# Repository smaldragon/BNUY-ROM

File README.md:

# BNUY-ROM

BNUY-ROM is an homebrew discrete logic mapper for the famicom/nes, which aims to have a similar level of capabilities to common ASIC mappers, while keeping a relatively low chip count. The mapper is designed to be modular, with features that can be included or ommitted depending on the needs of a game. It is similar to BNROM, hence the name.

Its capabilities are:

* Rewritable PRG-FLASH, 32K Window:
* * **39SF0x0** - Up to 512 KiB
* * **29FxxxFT** - Up to 2048KiB
* 32KiB PRG-RAM, 8K Window
* 8KiB, 32KiB or 128KiB of CHR-RAM, 4*2K Windows
* Fixed 4-Screen Nametable Arrangement
* Scanline IRQ, with MMC5-like timing

As an in-development mapper, there is currently no iNES number attributed, nor mainstream emulator support.

Render/schematic for the prototype tht version:

# Banks

* CPU $6000-$7FFF: 8KiB switchable PRG-RAM
* CPU $8000-$FFFF: 32 KiB switchable PRG-FLASH
* PPU $0000-$07FF: 2 KiB switchable CHR-RAM Bank
* PPU $0800-$0FFF: 2 KiB switchable CHR-RAM Bank
* PPU $1000-$17FF: 2 KiB switchable CHR-RAM Bank
* PPU $1800-$1FFF: 2 KiB switchable CHR-RAM Bank

# Registers

## PRG Banking ($8000-$9FFF, write)

This register controls the banking of PRG Flash and Ram.

```
A~100x xxxx xxxx xxxx ($8000)
D~7654 3210
  ---------
  RRPP PPPP
  ||++-++++--- PRG-Flash Bank
  ++-----------PRG-Ram Bank
```

## unused ($A000-$BFFF, write)

In previous iterations of the design, this area was used for a SAM2695 soundchip. It is now unused and avaliable for potential mapper additions.

## IRQ Counter Load ($C000-$DFFF, write)

This register will load a value into a scanline counter, which decrements once per active scanline at ppu cycle 4. The counter will continuously trigger an IRQ whenever its value is 0.

There is no mechanism to stop the counter, and it will underflow to 255 if an interrupt is ignored for 1 scanline. To stop the generator from firing, a value of 255 should be written every nmi.

```
A~110x xxxx xxxx xxxx ($C000)
D~7654 3210
  ---------
  IIII IIII
  ++++-++++- 8-bit scanline counter value
```

### Details

The 8-bit down counter is clocked by bit 2 of a prescaler counter, which increments on PPU reads with A13=1 and is cleared to zero on reads with A13=0. Normally one clock signal is generated by the prescaler per active scanline (including the pre-render scanline), but manual reads from PPU_DATA during VBlank or disabling rendering mid-frame will destabilize it. This can be overcome by reading once from A13=0 and twice from A13=1, followed by reloading the counter.

Overall the mechanism is similar to MMC5's scanline counter, but using relative values like the MMC3. Unlike the MMC3, this counter allows sprites to freely use either pattern table, including both while in 8x16 mode, and its timing simplifies scroll splits on consecutive scanlines.

It uses a x4520 to detect scanlines, and either a x40103 or two x191/x193s to hold the counter value.

## CHR Banking ($E000-$FFFF, write)

If present, these registers select one of 16 2KiB CHR-RAM banks, to use for each of the 4 PPU pattern table windows.

In **8k/linear mode**, the banking register is ommited. 16KiB of RAM are mapped to the PPU Address space, including 3840 bytes of "bonus ram" above the nametables, which the CPU may use to store values.

In **32K/shared mode**, Banks 0 and 15 are shared with the 4 nametables, and should be avoided unless special care is taken. This leaves 14 banks that can be freely distributed across the 4 windows. 

In **128K/independent mode**, the register is still 4 bits wide, but now each window has their own unique set of 16 banks (by connecting the top 2 address lines of memory to ppu A11/A12), this effectively quadruples the amount of avaliable chr-ram without adding a second register chip to the board. The first 2 windows share banks 15 with the nametables

```
A~111x xxxx xxxx xx00 ($E000)
	CHR Window 0
A~111x xxxx xxxx xx01 ($E001)
	CHR Window 1
A~111x xxxx xxxx xx10 ($E002)
	CHR Window 2
A~111x xxxx xxxx xx11 ($E003)
	CHR Window 3

D~7654 3210
  ---------
  .... BBBB
       ++++- CHR Bank Select
```

This uses a single x670 4x4 register. A second register could be added to the design for an oversize variant of 512KiB (shared) or 2048KiB (independent). A design with CHR-ROM could be used instead, at the cost of losing 4-screen nametable arrangement.

# Flash Programming

Flash programming is achieved by writing a specific sequence of command bytes to particular memory addresses, during this process flash memory cannot be read as normal, and conflicting mapper registers will have their values overwritten. As such, **flash programming code must be run from the internal 2KiB console ram, and all interrupts must be disabled**.

Flash writes operate by ANDing the written byte with the existing value in memory, with the only way to set a bit being by erasing an entire sector to `$FF`.

39SF commands listen to `A0-14`, which requires clobbering the IRQ Counter, while 29F commands listen only to `A0-A11`, allowing commands to fit in the unused `$A000-$BFFF` region.

For more information check the datasheet for your particular flash chip.

## Write Byte

### 39SF0x0

```
A~$8000 D~BANK
A~$D555 D~$AA
A~$AAAA D~$55
A~$D555 D~$A0
A~ADDR  D~DATA
```

### 29FxxxFT

```
A~$8000 D~BANK
A~$AAAA D~$AA
A~$A555 D~$55
A~$AAAA D~$A0
A~ADDR  D~DATA
```

## Erase Sector

### 39SF0x0

```
A~$8000 D~BANK
A~$D555 D~$AA
A~$AAAA D~$55
A~$D555 D~$80
A~$D555 D~$AA
A~$AAAA D~$55
A~ADDR  D~$30
```
**39SF0x0** uses uniform sectors of 4KiB,

### 29FxxxFT

```
A~$8000 D~BANK
A~$AAAA D~$AA
A~$A555 D~$55
A~$AAAA D~$80
A~$AAAA D~$AA
A~$A555 D~$55
A~ADDR  D~$30
```

**29FxxxFT** uses sectors of varying sizes depending on bank:
* Last Bank: 8KiB sectors at `$8000-$9FFF`, `$A000-$BFFF`, 16KiB sector at `$C000-$FFFF`
* Second-to-Last Bank: Single 32KiB sector
* All other banks: 64KiB sectors spanning 2 banks each.

## Write/Erase End Detect

The end of a write or erase operation can be detected by reading any memory address in flash until the same value is returned twice (toggle bit method).

## Software ID

Software ID mode can be entered to detect the manufacturer, size and type of flash chip, allowing for the same rom file to be compatible with multiple board configurations. Software ID is entered using the following command sequences:

### 39SF0x0

```
A~$8000 D~$00
A~$D555 D~$AA
A~$AAAA D~$55
A~$D555 D~$90
```

### 29FxxxFT

```
A~$8000 D~$00
A~$AAAA D~$AA
A~$A555 D~$55
A~$AAAA D~$90
```

Software ID mode is exited by writing `$F0` anywhere in flash.

### Device Code ($8001, read)

* `$B5` - 39SF010 (128KiB)
* `$B6` - 39SF020 (256KiB)
* `$B7` - 39SF040  (512KiB)
* `$51` - 29F200FT (256KiB)
* `$23` - 29F400FT (512KiB)
* `$D6` - 29F800FT (1024KiB)
* `$D2` - 29F160FT (2048KiB)

# NES 2.0 Description (tentative)

**Mapper ID**: *Unassigned*

**Flags 6 (nametable layout/flashing)**

```
D~3210
  ----
  F0BM
  | |+-- Hard-Wired Arragement
  | |      0: Vertical / 4-screen
  | |      1: Horizontal
  | +--- Uses Flash Saves
  |        0: No
  |        1: Yes
  +----- 4-Screen Arrangement
           0: Hard-Wired (using CIRAM)
           1: 4-Screen (using CHR-RAM)
```

Most games will have `%1010` here.

**Flags 8 (submapper)**

```
D~7654
  ----
  FICC
  ||++-- CHR Banking Mode
  ||        0: 8K/Linear (no banking)
  ||        1: 32K/Shared (all banks avaliable in every window)
  ||        2: 128K/Independent (all windows have unique sets of banks)
  |+---- Interrupt Generator
  |         0: No IRQ
  |         1: Has IRQ
  +----- Flash Memory Type
            0: 39SF0x0 (sizes of 128K, 256K, 512K)
            1: 29FxxxFT (sizes of 256K, 512K, 1024K, 2048K)
```

**PRG-ROM, PRG-RAM and CHR-RAM size**

Size should match the memory accessible on the board.

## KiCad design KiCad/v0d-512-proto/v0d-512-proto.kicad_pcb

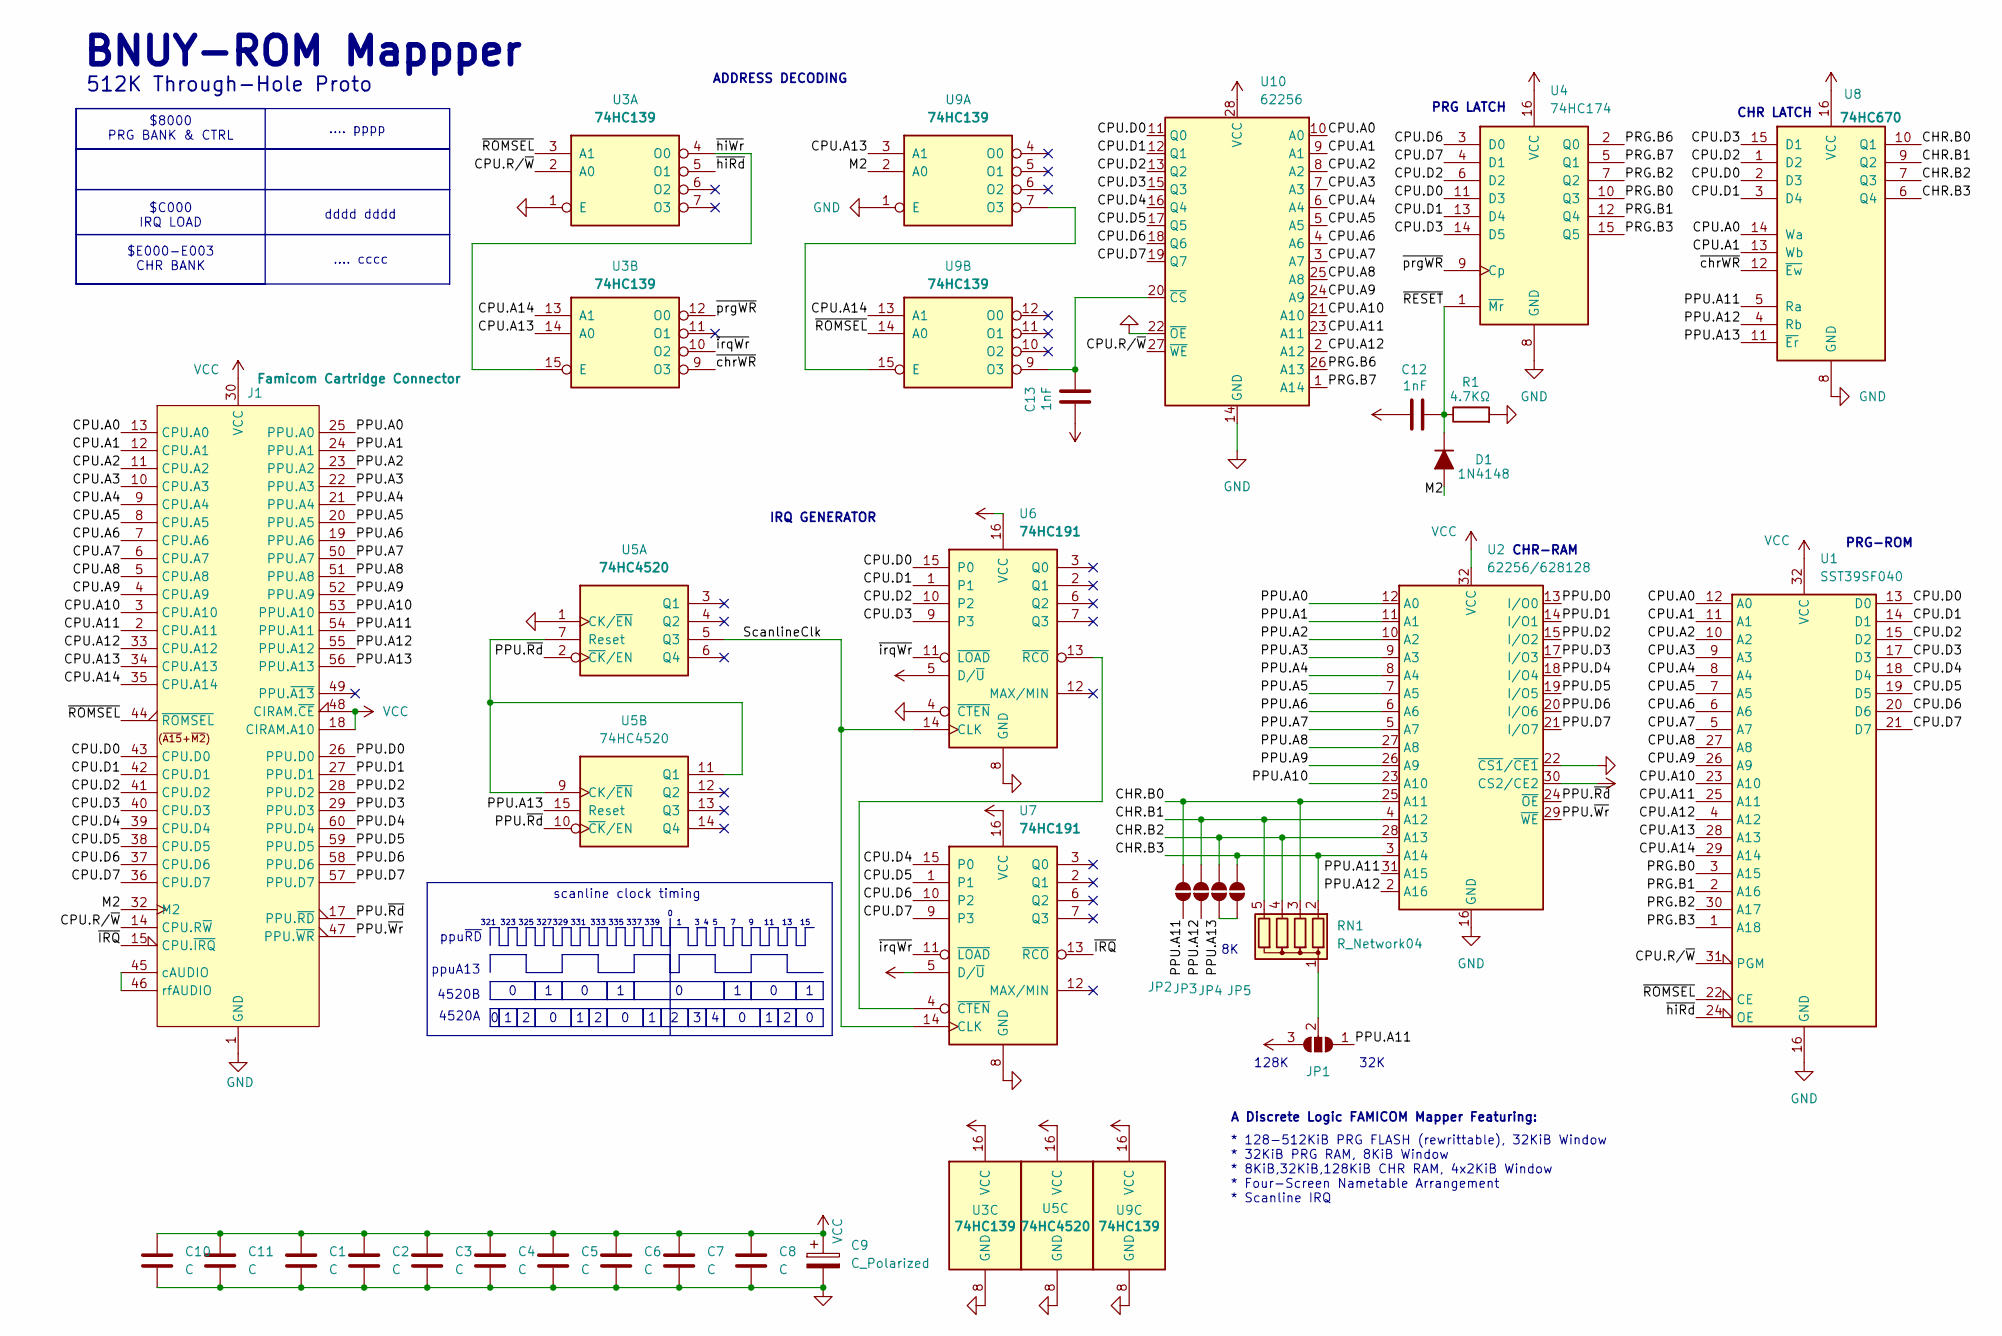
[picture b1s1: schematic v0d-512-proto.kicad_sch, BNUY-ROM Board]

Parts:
C1, C2, C3, C4, C5, C6, C7, C8, C10, C11: C; C_Disc_D3.0mm_W1.6mm_P2.50mm
C9: C_Polarized; CP_Radial_D5.0mm_P2.50mm
C12, C13: 1nF; C_Disc_D3.0mm_W1.6mm_P2.50mm
D1: 1N4148; D_DO-35_SOD27_P2.54mm_Vertical_AnodeUp
J1: Famicom Cartridge Connector; Famicom Cartridge Edge Connector (long legs)
JP1: SolderJumper_3_Open; SolderJumper-3_P1.3mm_Open_Pad1.0x1.5mm_NumberLabels
JP2, JP3, JP4, JP5: SolderJumper_2_Open; SolderJumper-2_P1.3mm_Open_Pad1.0x1.5mm
R1: 4.7KΩ; R_Axial_DIN0204_L3.6mm_D1.6mm_P2.54mm_Vertical
RN1: R_Network04; R_Array_SIP5
U1: SST39SF040; PLCC-DIP-32_THT-Socket
U2: 62256/628128; DIP-32_W15.24mm
U3, U9: 74HC139; DIP-16_W7.62mm
U4: 74HC174; DIP-16_W7.62mm
U5: 74HC4520; DIP-16_W7.62mm
U6, U7: 74HC191; DIP-16_W7.62mm
U8: 74HC670; DIP-16_W7.62mm
U10: 62256; DIP-28_W15.24mm

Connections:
/CHR.B0: JP2.1 (A), RN1.3 (R2), U2.25 (A11), U8.10 (Q1)
/CHR.B1: JP3.1 (A), RN1.5 (R4), U2.4 (A12), U8.9 (Q2)
/CHR.B2: JP4.1 (A), RN1.4 (R3), U2.28 (A13), U8.7 (Q3)
/CHR.B3: JP5.1 (A), RN1.2 (R1), U2.3 (A14), U8.6 (Q4)
/CPU.A0: J1.13 (CPU.A0), U1.12 (A0), U8.14 (Wa), U10.10 (A0)
/CPU.A1: J1.12 (CPU.A1), U1.11 (A1), U8.13 (Wb), U10.9 (A1)
/CPU.A2: J1.11 (CPU.A2), U1.10 (A2), U10.8 (A2)
/CPU.A3: J1.10 (CPU.A3), U1.9 (A3), U10.7 (A3)
/CPU.A4: J1.9 (CPU.A4), U1.8 (A4), U10.6 (A4)
/CPU.A5: J1.8 (CPU.A5), U1.7 (A5), U10.5 (A5)
/CPU.A6: J1.7 (CPU.A6), U1.6 (A6), U10.4 (A6)
/CPU.A7: J1.6 (CPU.A7), U1.5 (A7), U10.3 (A7)
/CPU.A8: J1.5 (CPU.A8), U1.27 (A8), U10.25 (A8)
/CPU.A9: J1.4 (CPU.A9), U1.26 (A9), U10.24 (A9)
/CPU.A10: J1.3 (CPU.A10), U1.23 (A10), U10.21 (A10)
/CPU.A11: J1.2 (CPU.A11), U1.25 (A11), U10.23 (A11)
/CPU.A12: J1.33 (CPU.A12), U1.4 (A12), U10.2 (A12)
/CPU.A13: J1.34 (CPU.A13), U1.28 (A13), U3.14 (A0), U9.3 (A1)
/CPU.A14: J1.35 (CPU.A14), U1.29 (A14), U3.13 (A1), U9.13 (A1)
/CPU.D0: J1.43 (CPU.D0), U1.13 (D0), U4.11 (D3), U6.15 (P0), U8.2 (D3), U10.11 (Q0)
/CPU.D1: J1.42 (CPU.D1), U1.14 (D1), U4.13 (D4), U6.1, U8.3 (D4), U10.12 (Q1)
/CPU.D2: J1.41 (CPU.D2), U1.15 (D2), U4.6 (D2), U6.10 (P2), U8.1 (D2), U10.13 (Q2)
/CPU.D3: J1.40 (CPU.D3), U1.17 (D3), U4.14 (D5), U6.9 (P3), U8.15 (D1), U10.15 (Q3)
/CPU.D4: J1.39 (CPU.D4), U1.18 (D4), U7.15 (P0), U10.16 (Q4)
/CPU.D5: J1.38 (CPU.D5), U1.19 (D5), U7.1, U10.17 (Q5)
/CPU.D6: J1.37 (CPU.D6), U1.20 (D6), U4.3 (D0), U7.10 (P2), U10.18 (Q6)
/CPU.D7: J1.36 (CPU.D7), U1.21 (D7), U4.4 (D1), U7.9 (P3), U10.19 (Q7)
/CPU.R/~W: J1.14 (CPU.R~W), U1.31 (PGM), U3.2 (A0), U10.27 (~WE)
/M2: D1.2 (A), J1.32 (M2), U9.2 (A0)
/PPU.A0: J1.25 (PPU.A0), U2.12 (A0)
/PPU.A1: J1.24 (PPU.A1), U2.11 (A1)
/PPU.A2: J1.23 (PPU.A2), U2.10 (A2)
/PPU.A3: J1.22 (PPU.A3), U2.9 (A3)
/PPU.A4: J1.21 (PPU.A4), U2.8 (A4)
/PPU.A5: J1.20 (PPU.A5), U2.7 (A5)
/PPU.A6: J1.19 (PPU.A6), U2.6 (A6)
/PPU.A7: J1.50 (PPU.A7), U2.5 (A7)
/PPU.A8: J1.51 (PPU.A8), U2.27 (A8)
/PPU.A9: J1.52 (PPU.A9), U2.26 (A9)
/PPU.A10: J1.53 (PPU.A10), U2.23 (A10)
/PPU.A11: J1.54 (PPU.A11), JP1.1 (A), JP2.2 (B), U2.31 (A15), U8.5 (Ra)
/PPU.A12: J1.55 (PPU.A12), JP3.2 (B), U2.2 (A16), U8.4 (Rb)
/PPU.A13: J1.56 (PPU.A13), JP4.2 (B), JP5.2 (B), U5.15 (Reset), U8.11 (~Er)
/PPU.D0: J1.26 (PPU.D0), U2.13 (I/O0)
/PPU.D1: J1.27 (PPU.D1), U2.14 (I/O1)
/PPU.D2: J1.28 (PPU.D2), U2.15 (I/O2)
/PPU.D3: J1.29 (PPU.D3), U2.17 (I/O3)
/PPU.D4: J1.60 (PPU.D4), U2.18 (I/O4)
/PPU.D5: J1.59 (PPU.D5), U2.19 (I/O5)
/PPU.D6: J1.58 (PPU.D6), U2.20 (I/O6)
/PPU.D7: J1.57 (PPU.D7), U2.21 (I/O7)
/PPU.~Rd: J1.17 (PPU.~RD), U2.24 (~OE), U5.2 (~CK/EN), U5.10 (~CK/EN)
/PPU.~Wr: J1.47 (PPU.~WR), U2.29 (~WE)
/PRG.B0: U1.3 (A15), U4.10 (Q3)
/PRG.B1: U1.2 (A16), U4.12 (Q4)
/PRG.B2: U1.30 (A17), U4.7 (Q2)
/PRG.B3: U1.1 (A18), U4.15 (Q5)
/PRG.B6: U4.2 (Q0), U10.26 (A13)
/PRG.B7: U4.5 (Q1), U10.1 (A14)
/ScanlineClk: U5.5 (Q3), U6.14 (CLK), U7.14 (CLK)
/~IRQ: J1.15 (CPU.~IRQ), U7.13 (~RCO)
/~RESET: C12.2, D1.1 (K), R1.1, U4.1 (~Mr)
/~ROMSEL: J1.44 (~ROMSEL), U1.22 (CE), U3.3 (A1), U9.14 (A0)
/~chrWR: U3.9 (O3), U8.12 (~Ew)
/~hiRd: U1.24 (OE), U3.5 (O1)
/~hiWr: U3.4 (O0), U3.15 (E)
/~irqWr: U3.10 (O2), U6.11 (~LOAD), U7.11 (~LOAD)
/~prgWR: U3.12 (O0), U4.9 (Cp)
GND: C1.2, C2.2, C3.2, C4.2, C5.2, C6.2, C7.2, C8.2, C9.2, C10.2, C11.2, J1.1 (GND), J1.16 (GND), R1.2, U1.16 (GND), U2.16 (GND), U2.22 (~CS1/~CE1), U3.1 (E), U3.8 (GND), U4.8 (GND), U5.1 (CK/~EN), U5.8 (GND), U6.4 (~CTEN), U6.8 (GND), U7.8 (GND), U8.8 (GND), U9.1 (E), U9.8 (GND), U10.14 (GND), U10.22 (~OE)
unnamed: J1.45 (cAUDIO), J1.46 (rfAUDIO)
unnamed: JP1.2 (C), RN1.1 (common)
unnamed: U5.7 (Reset), U5.9 (CK/~EN), U5.11 (Q1)
unnamed: U6.13 (~RCO), U7.4 (~CTEN)
unnamed: U9.7 (O3), U9.15 (E)
unnamed: C13.2, U9.9 (O3), U10.20 (~CS)
VCC: C1.1, C2.1, C3.1, C4.1, C5.1, C6.1, C7.1, C8.1, C9.1, C10.1, C11.1, C12.1, C13.1, J1.18 (CIRAM.A10), J1.30 (VCC), J1.31 (VCC), J1.48 (CIRAM.~CE), JP1.3 (B), U1.32 (VCC), U2.30 (CS2/CE2), U2.32 (VCC), U3.16 (VCC), U4.16 (VCC), U5.16 (VCC), U6.5 (D/~U), U6.16 (VCC), U7.5 (D/~U), U7.16 (VCC), U8.16 (VCC), U9.16 (VCC), U10.28 (VCC)

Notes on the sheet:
BNUY-ROM Mappper
335
321
.... pppp
* 128-512KiB PRG FLASH (rewrittable), 32KiB Window * 32KiB PRG RAM, 8KiB Window * 8KiB,32KiB,128KiB CHR RAM, 4x2KiB Window * Four-Screen Nametable Arrangement * Scanline IRQ
325
512K Through-Hole Proto
4520B
ADDRESS DECODING
327
339
ppuA13
CHR-RAM
dddd dddd
333
337
.... cccc
4520A
329
CHR LATCH
323
128K
A Discrete Logic FAMICOM Mapper Featuring:
PRG-ROM
scanline clock timing
IRQ GENERATOR
PRG LATCH
32K
331
ppu~{RD}
$8000 PRG BANK & CTRL $C000 IRQ LOAD $E000-E003 CHR BANK

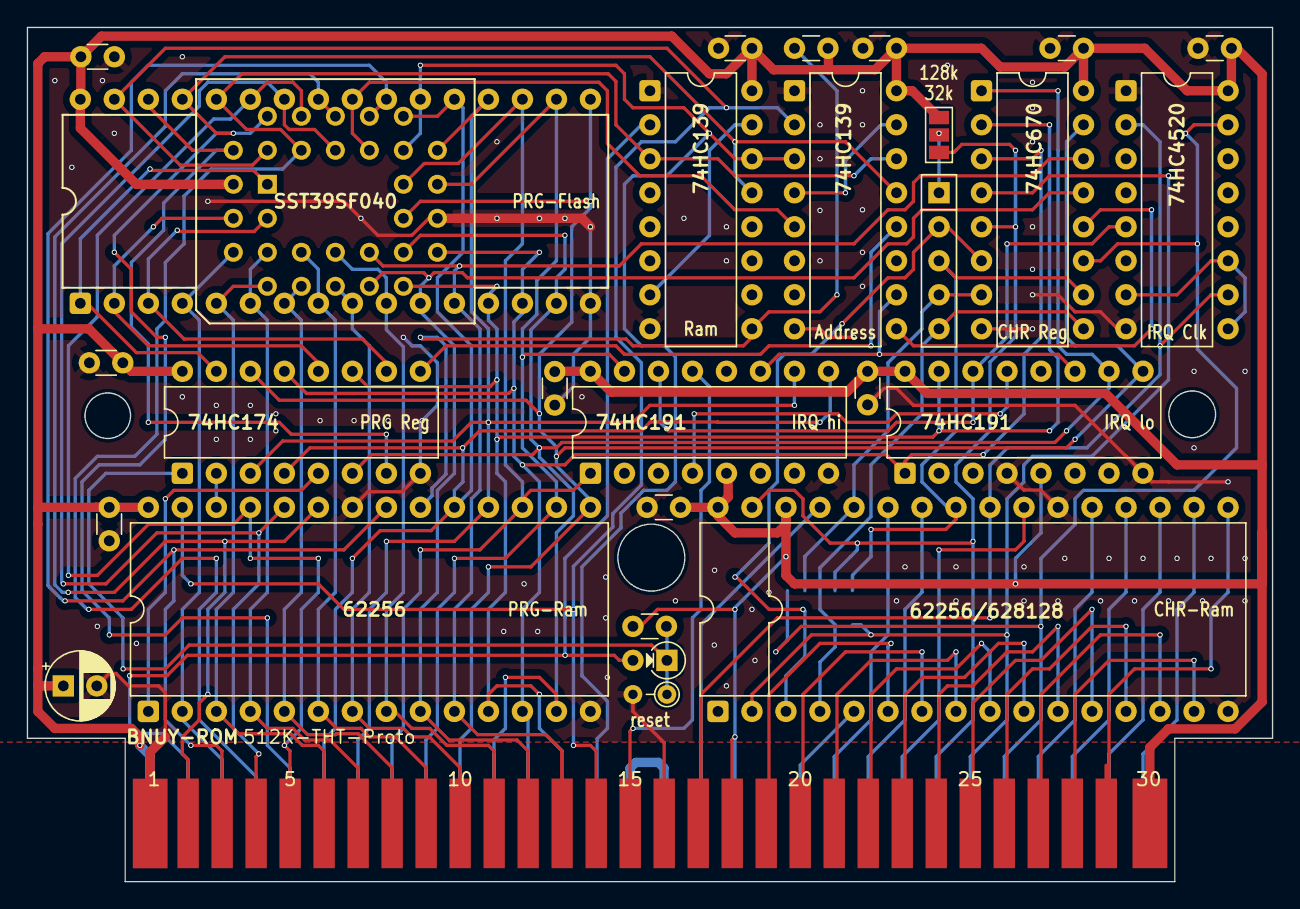
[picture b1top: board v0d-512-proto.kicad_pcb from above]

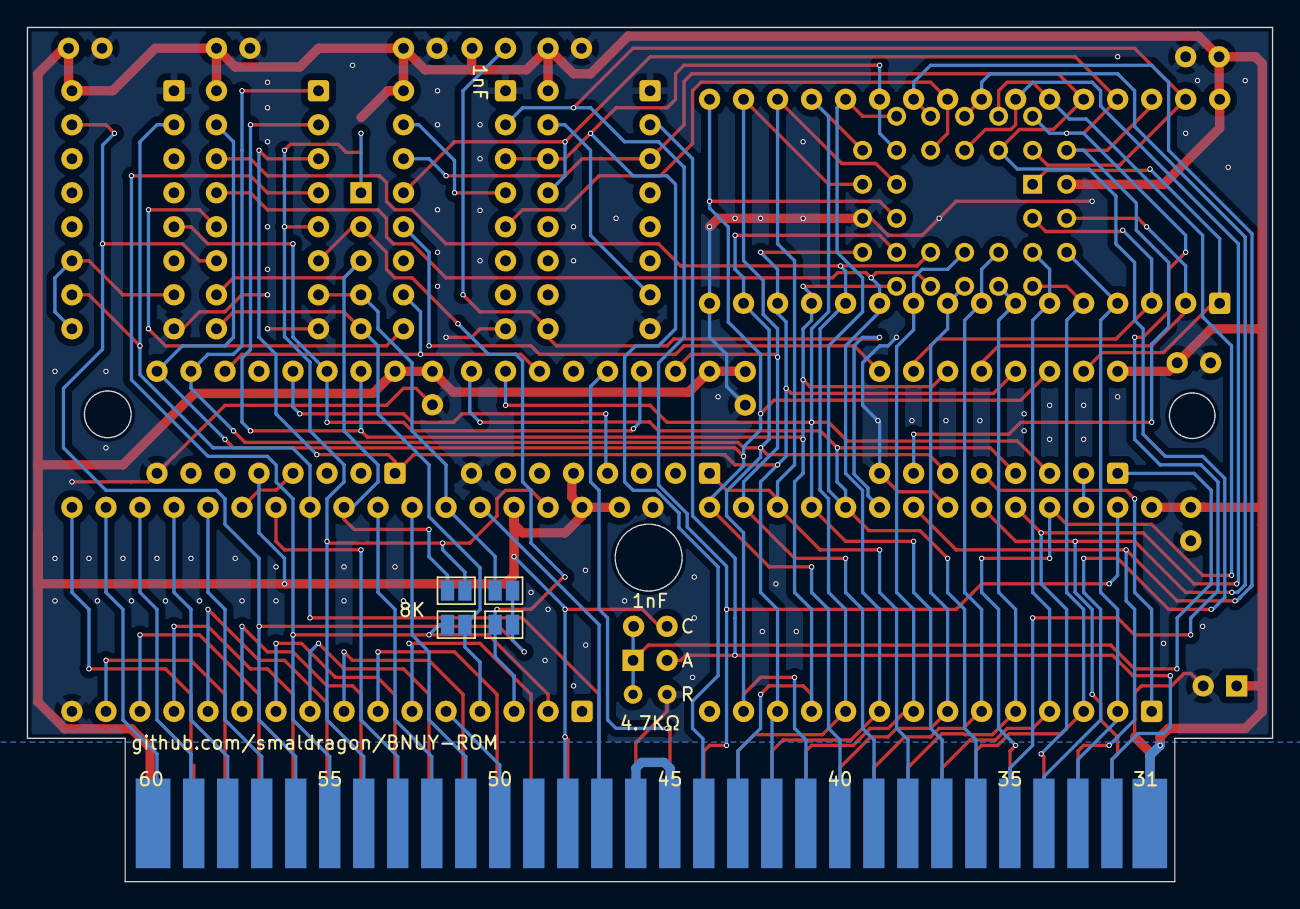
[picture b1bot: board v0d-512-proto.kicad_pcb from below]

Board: 2 copper layers, 93.0 x 63.8 mm, 32 parts (4 on the bottom side), 76 nets.

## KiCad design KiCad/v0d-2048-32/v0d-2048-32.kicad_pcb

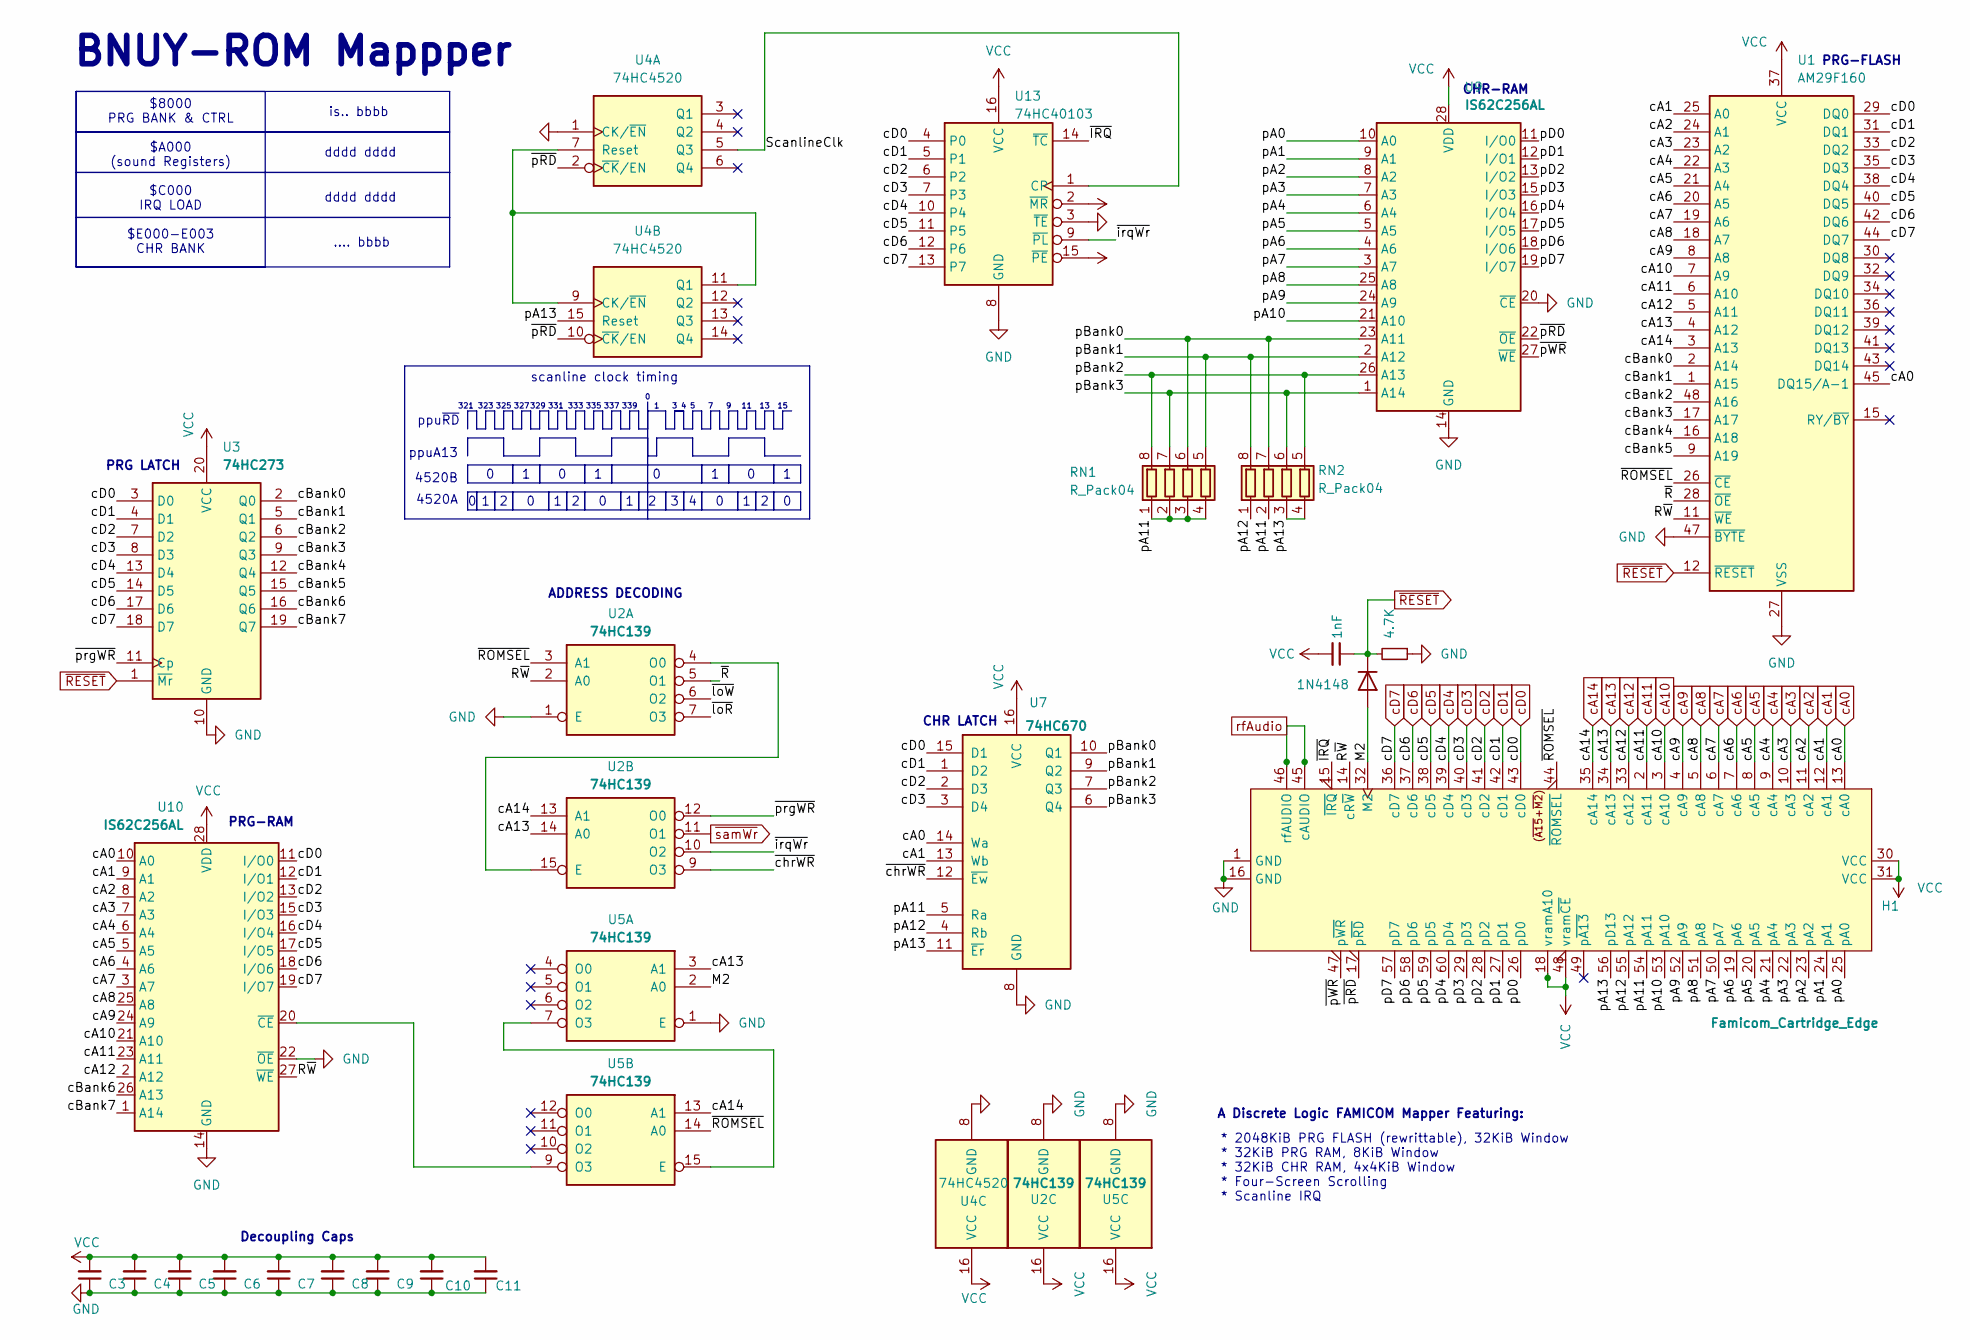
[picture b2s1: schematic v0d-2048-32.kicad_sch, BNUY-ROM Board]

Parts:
C1: 1nF; C_0603_1608Metric_Pad1.08x0.95mm_HandSolder
C3, C4, C5, C6, C7, C8, C9, C10, C11: C_Small; C_0603_1608Metric_Pad1.08x0.95mm_HandSolder
D1: 1N4148; D_0603_1608Metric_Pad1.05x0.95mm_HandSolder
H1: Famicom_Cartridge_Edge; Famicom Cartridge Edge Connector (long legs)
R1: 4.7K; R_0603_1608Metric_Pad1.05x0.95mm_HandSolder
RN1, RN2: R_Pack04; R_Array_Convex_4x0603
U1: AM29F160; TSOP-I-48_18.4x12mm_P0.5mm
U2, U5: 74HC139; SOIC-16_3.9x9.9mm_P1.27mm
U3: 74HC273; SOIC-20W_7.5x12.8mm_P1.27mm
U4: 74HC4520; SOIC-16_3.9x9.9mm_P1.27mm
U7: 74HC670; SOIC-16_3.9x9.9mm_P1.27mm
U9, U10: IS62C256AL; TSOP-I-28_11.8x8mm_P0.55mm_MiddlePin
U13: 74HC40103; SOIC-16_3.9x9.9mm_P1.27mm

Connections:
/M2: D1.2 (A), H1.32 (M2), U5.2 (A0)
/R~W: H1.14 (cR~W), U1.11 (~WE), U2.2 (A0), U10.27 (~WE)
/ScanlineClk: U4.5 (Q3), U13.1 (CP)
/cBank0: U1.2 (A14), U3.2 (Q0)
/cBank1: U1.1 (A15), U3.5 (Q1)
/cBank2: U1.48 (A16), U3.6 (Q2)
/cBank3: U1.17 (A17), U3.9 (Q3)
/cBank4: U1.16 (A18), U3.12 (Q4)
/cBank5: U1.9 (A19), U3.15 (Q5)
/cBank6: U3.16 (Q6), U10.26 (A13)
/cBank7: U3.19 (Q7), U10.1 (A14)
/pA0: H1.25 (pA0), U9.10 (A0)
/pA1: H1.24 (pA1), U9.9 (A1)
/pA2: H1.23 (pA2), U9.8 (A2)
/pA3: H1.22 (pA3), U9.7 (A3)
/pA4: H1.21 (pA4), U9.6 (A4)
/pA5: H1.20 (pA5), U9.5 (A5)
/pA6: H1.19 (pA6), U9.4 (A6)
/pA7: H1.50 (pA7), U9.3 (A7)
/pA8: H1.51 (pA8), U9.25 (A8)
/pA9: H1.52 (pA9), U9.24 (A9)
/pA10: H1.53 (pA10), U9.21 (A10)
/pA11: H1.54 (pA11), RN1.1 (R1.1), RN1.2 (R2.1), RN1.3 (R3.1), RN1.4 (R4.1), RN2.2 (R2.1), U7.5 (Ra)
/pA12: H1.55 (pA12), RN2.1 (R1.1), U7.4 (Rb)
/pA13: H1.56 (pD13), RN2.3 (R3.1), RN2.4 (R4.1), U4.15 (Reset), U7.11 (~Er)
/pBank0: RN1.6 (R3.2), RN2.7 (R2.2), U7.10 (Q1), U9.23 (A11)
/pBank1: RN1.5 (R4.2), RN2.8 (R1.2), U7.9 (Q2), U9.2 (A12)
/pBank2: RN1.8 (R1.2), RN2.5 (R4.2), U7.7 (Q3), U9.26 (A13)
/pBank3: RN1.7 (R2.2), RN2.6 (R3.2), U7.6 (Q4), U9.1 (A14)
/pD0: H1.26 (pD0), U9.11 (I/O0)
/pD1: H1.27 (pD1), U9.12 (I/O1)
/pD2: H1.28 (pD2), U9.13 (I/O2)
/pD3: H1.29 (pD3), U9.15 (I/O3)
/pD4: H1.60 (pD4), U9.16 (I/O4)
/pD5: H1.59 (pD5), U9.17 (I/O5)
/pD6: H1.58 (pD6), U9.18 (I/O6)
/pD7: H1.57 (pD7), U9.19 (I/O7)
/~IRQ: H1.15 (~IRQ), U13.14 (~TC)
/~ROMSEL: H1.44 (~ROMSEL), U1.26 (~CE), U2.3 (A1), U5.14 (A0)
/~R: U1.28 (~OE), U2.5 (O1)
/~chrWR: U2.9 (O3), U7.12 (~Ew)
/~irqWr: U2.10 (O2), U13.9 (~PL)
/~loR: U2.7 (O3)
/~loW: U2.6 (O2)
/~pRD: H1.17 (p~RD), U4.2 (~CK/EN), U4.10 (~CK/EN), U9.22 (~OE)
/~pWR: H1.47 (p~WR), U9.27 (~WE)
/~prgWR: U2.12 (O0), U3.11 (Cp)
GND: C3.1, C4.1, C5.1, C6.1, C7.1, C8.1, C9.1, C10.1, C11.1, H1.1 (GND), H1.16 (GND), R1.1, U1.27 (VSS), U1.47 (~BYTE), U2.1 (E), U2.8 (GND), U3.10 (GND), U4.1 (CK/~EN), U4.8 (GND), U5.1 (E), U5.8 (GND), U7.8 (GND), U9.14 (GND), U9.20 (~CE), U10.14 (GND), U10.22 (~OE), U13.3 (~TE), U13.8 (GND)
unnamed: U2.4 (O0), U2.15 (E)
unnamed: U4.7 (Reset), U4.9 (CK/~EN), U4.11 (Q1)
unnamed: U5.7 (O3), U5.15 (E)
unnamed: U5.9 (O3), U10.20 (~CE)
VCC: C1.2, C3.2, C4.2, C5.2, C6.2, C7.2, C8.2, C9.2, C10.2, C11.2, H1.18 (vramA10), H1.30 (VCC), H1.31 (VCC), H1.48 (vram~CE), U1.37 (VCC), U2.16 (VCC), U3.20 (VCC), U4.16 (VCC), U5.16 (VCC), U7.16 (VCC), U9.28 (VDD), U10.28 (VDD), U13.2 (~MR), U13.15 (~PE), U13.16 (VCC)
cA0: H1.13 (cA0), U1.45 (DQ15/A-1), U7.14 (Wa), U10.10 (A0)
cA1: H1.12 (cA1), U1.25 (A0), U7.13 (Wb), U10.9 (A1)
cA2: H1.11 (cA2), U1.24 (A1), U10.8 (A2)
cA3: H1.10 (cA3), U1.23 (A2), U10.7 (A3)
cA4: H1.9 (cA4), U1.22 (A3), U10.6 (A4)
cA5: H1.8 (cA5), U1.21 (A4), U10.5 (A5)
cA6: H1.7 (cA6), U1.20 (A5), U10.4 (A6)
cA7: H1.6 (cA7), U1.19 (A6), U10.3 (A7)
cA8: H1.5 (cA8), U1.18 (A7), U10.25 (A8)
cA9: H1.4 (cA9), U1.8 (A8), U10.24 (A9)
cA10: H1.3 (cA10), U1.7 (A9), U10.21 (A10)
cA11: H1.2 (cA11), U1.6 (A10), U10.23 (A11)
cA12: H1.33 (cA12), U1.5 (A11), U10.2 (A12)
cA13: H1.34 (cA13), U1.4 (A12), U2.14 (A0), U5.3 (A1)
cA14: H1.35 (cA14), U1.3 (A13), U2.13 (A1), U5.13 (A1)
cD0: H1.43 (cD0), U1.29 (DQ0), U3.3 (D0), U7.15 (D1), U10.11 (I/O0), U13.4 (P0)
cD1: H1.42 (cD1), U1.31 (DQ1), U3.4 (D1), U7.1 (D2), U10.12 (I/O1), U13.5 (P1)
cD2: H1.41 (cD2), U1.33 (DQ2), U3.7 (D2), U7.2 (D3), U10.13 (I/O2), U13.6 (P2)
cD3: H1.40 (cD3), U1.35 (DQ3), U3.8 (D3), U7.3 (D4), U10.15 (I/O3), U13.7 (P3)
cD4: H1.39 (cD4), U1.38 (DQ4), U3.13 (D4), U10.16 (I/O4), U13.10 (P4)
cD5: H1.38 (cD5), U1.40 (DQ5), U3.14 (D5), U10.17 (I/O5), U13.11 (P5)
cD6: H1.37 (cD6), U1.42 (DQ6), U3.17 (D6), U10.18 (I/O6), U13.12 (P6)
cD7: H1.36 (cD7), U1.44 (DQ7), U3.18 (D7), U10.19 (I/O7), U13.13 (P7)
rfAudio: H1.45 (cAUDIO), H1.46 (rfAUDIO)
~RESET: C1.1, D1.1 (K), R1.2, U1.12 (~RESET), U3.1 (~Mr)
~samWr: U2.11 (O1)

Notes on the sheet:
BNUY-ROM Mappper
335
321
is.. bbbb
* 2048KiB PRG FLASH (rewrittable), 32KiB Window * 32KiB PRG RAM, 8KiB Window * 32KiB CHR RAM, 4x4KiB Window * Four-Screen Scrolling * Scanline IRQ
325
4520B
ADDRESS DECODING
327
339
ppuA13
CHR-RAM
dddd dddd
333
337
.... bbbb
4520A
PRG-RAM
329
CHR LATCH
323
A Discrete Logic FAMICOM Mapper Featuring:
Decoupling Caps
PRG-FLASH
scanline clock timing
PRG LATCH
331
ppu~{RD}
$8000 PRG BANK & CTRL $A000 (sound Registers) $C000 IRQ LOAD $E000-E003 CHR BANK

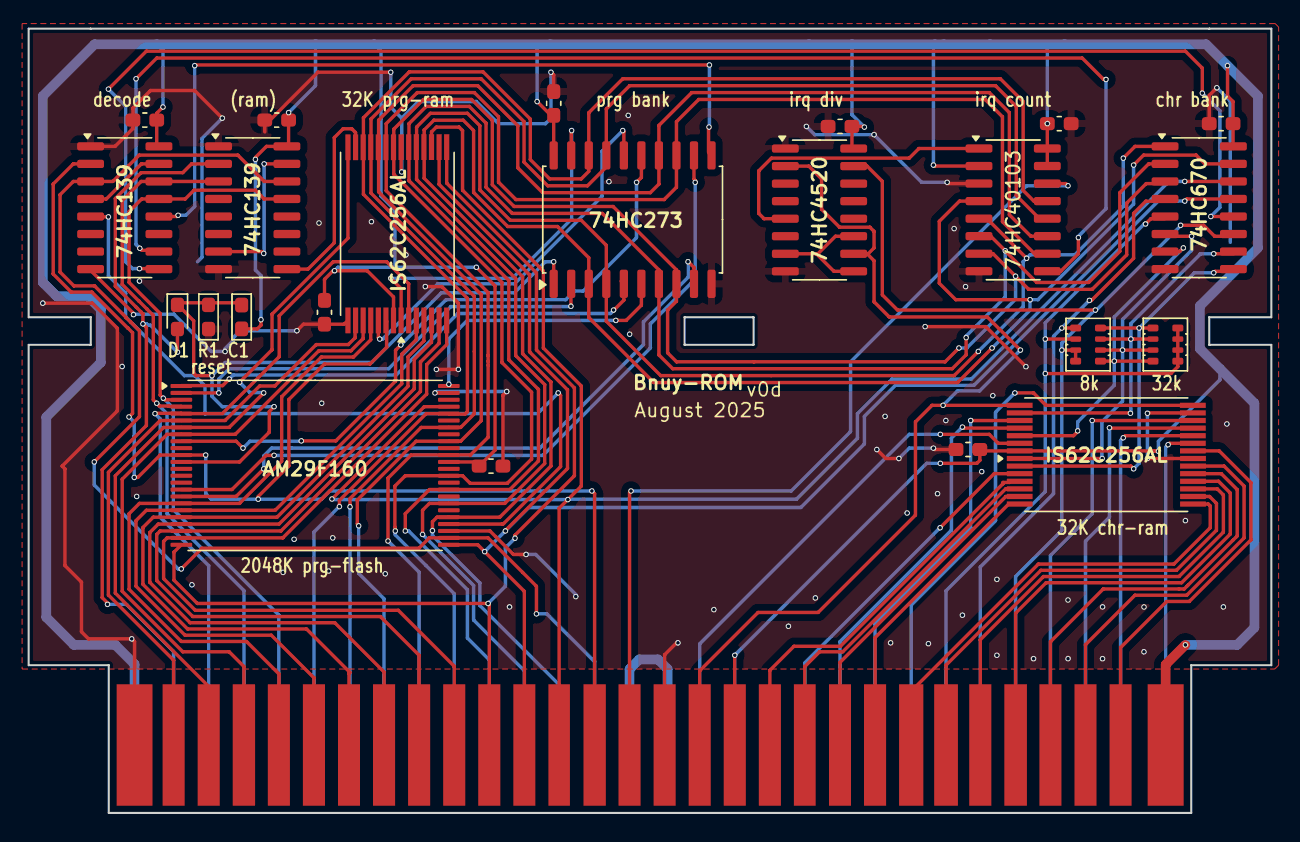
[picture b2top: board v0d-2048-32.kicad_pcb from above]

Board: 2 copper layers, 90.0 x 56.8 mm, 24 parts (0 on the bottom side), 76 nets.
